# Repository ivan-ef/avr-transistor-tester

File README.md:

# AVR Transistor Tester

Component/Transistor tester based on famous [AVR Transistor Tester](https://www.mikrocontroller.net/articles/AVR_Transistortester) project. The reason I decided to create a custom PCB is that currently there is not good kit or complete device available that would fit my wishes:

- ATMega644 MCU
- 2.4" 65K colors LCD
- Rotary encoder
- USB-C charger with Li-Po battery
- Higher grade/precision components

Most of Chinese versions are starting to use fake or non-original Microchip MCUs that prevents their software upgrades and economy on components makes them less accurate. I didn't include a lot of hardware options, because I primarily using the device for measuring passive components and transistors used in guitar pedals building.

## Complete unit

## PCB

I used SMD assembly service at JLCPCB and ended up with a set 5 PCBs cost around 25$ each. But since SMD components used there is not the smallest size ones, it is 100% possible to solder everything by hand.

## Schematic

[PDF](https://github.com/vitaliy-bobrov/avr-transistor-tester/blob/main/schematic.pdf)

## Hardware

PCB has almost everything as SMD assembly and requires a few components to be soldered by hand:

- Rotary Encoder - basically any common one would work here, but I've used BOURNS PEC11R-4220K-S0024. It is available at most big components suppliers. My personal choice was [TME](https://www.tme.eu/pl/details/pec11r-4220k-s0024/enkodery-inkrementalne/bourns/).
- ZIF 14 pin socket - again you could use any common one. I used CONNFLY DS1044-140G from [TME](https://www.tme.eu/pl/details/ds1044-140g/podstawki-testowe/connfly/)
- 2.4" 65K colors LCB. Not sure if other ILI9341 controller based would have the same pins/size. I used [Waveshare 18366](https://www.waveshare.com/2.4inch-lcd-module.htm) which is not expensive and commonly available. At [TME](https://www.tme.eu/pl/details/wsh-18366/wyswietlacze-lcd-graficzne/waveshare/18366/) too ;)
- 2.54mm spaced 2x3 pins for ISP - this could be left without pins soldered, then just ensure you have good contact between the PCB and programming pins.
- 2.54mm 3 pin socket for components/transistors - just alternative for ZIF socket
- Any Li-Po or Li-Ion battery with work with the charger IC, but the PCB was designed with Li-Po in mind due to size. I used [550mA battery](https://www.tme.eu/pl/details/aky-lp503040/akumulatory/akyga-battery/aky0185/), but you could use any other that would fit about 55x50mm size.

## Software

The software used in m-software version 1.55m (see [docs](https://github.com/madires/Transistortester-Warehouse/tree/master/Documentation)), but k-software could be used as well. The pins assignment is based on project docs suggested one. Precompiled version is in the [software](https://github.com/vitaliy-bobrov/avr-transistor-tester/blob/main/software/) folder.

### Software compilation

1. Install AVR tools for your operating system and programmer you are using (ex. avrdude)
2. Navigate to software folder
3. Run `make`
4. Connect programmer to the ISP pins on the PCB
5. Run `make fuses` to set MCU fuses
6. Run `make upload` to upload firmware

## Enclosure

I designed a simple 3D printable enclosure that fits the PCB and provides easy access to ISP pins and USB-C charger. STEP files are located in the [3d-enclosure](https://github.com/vitaliy-bobrov/avr-transistor-tester/blob/main/3d-enclosure/) folder. Printing profile is available at [MakerWorld](https://makerworld.com/en/models/883799#profileId-838469) which would be handy if you have a BambuLab 3D printer.

The assembled PCB with display is mounted to enclosure using spacers that came with Waveshare display using 4 x M2x8mm and 4 x M2x16mm screws. the battery is fixed on the backplate with double sided 3M foam.

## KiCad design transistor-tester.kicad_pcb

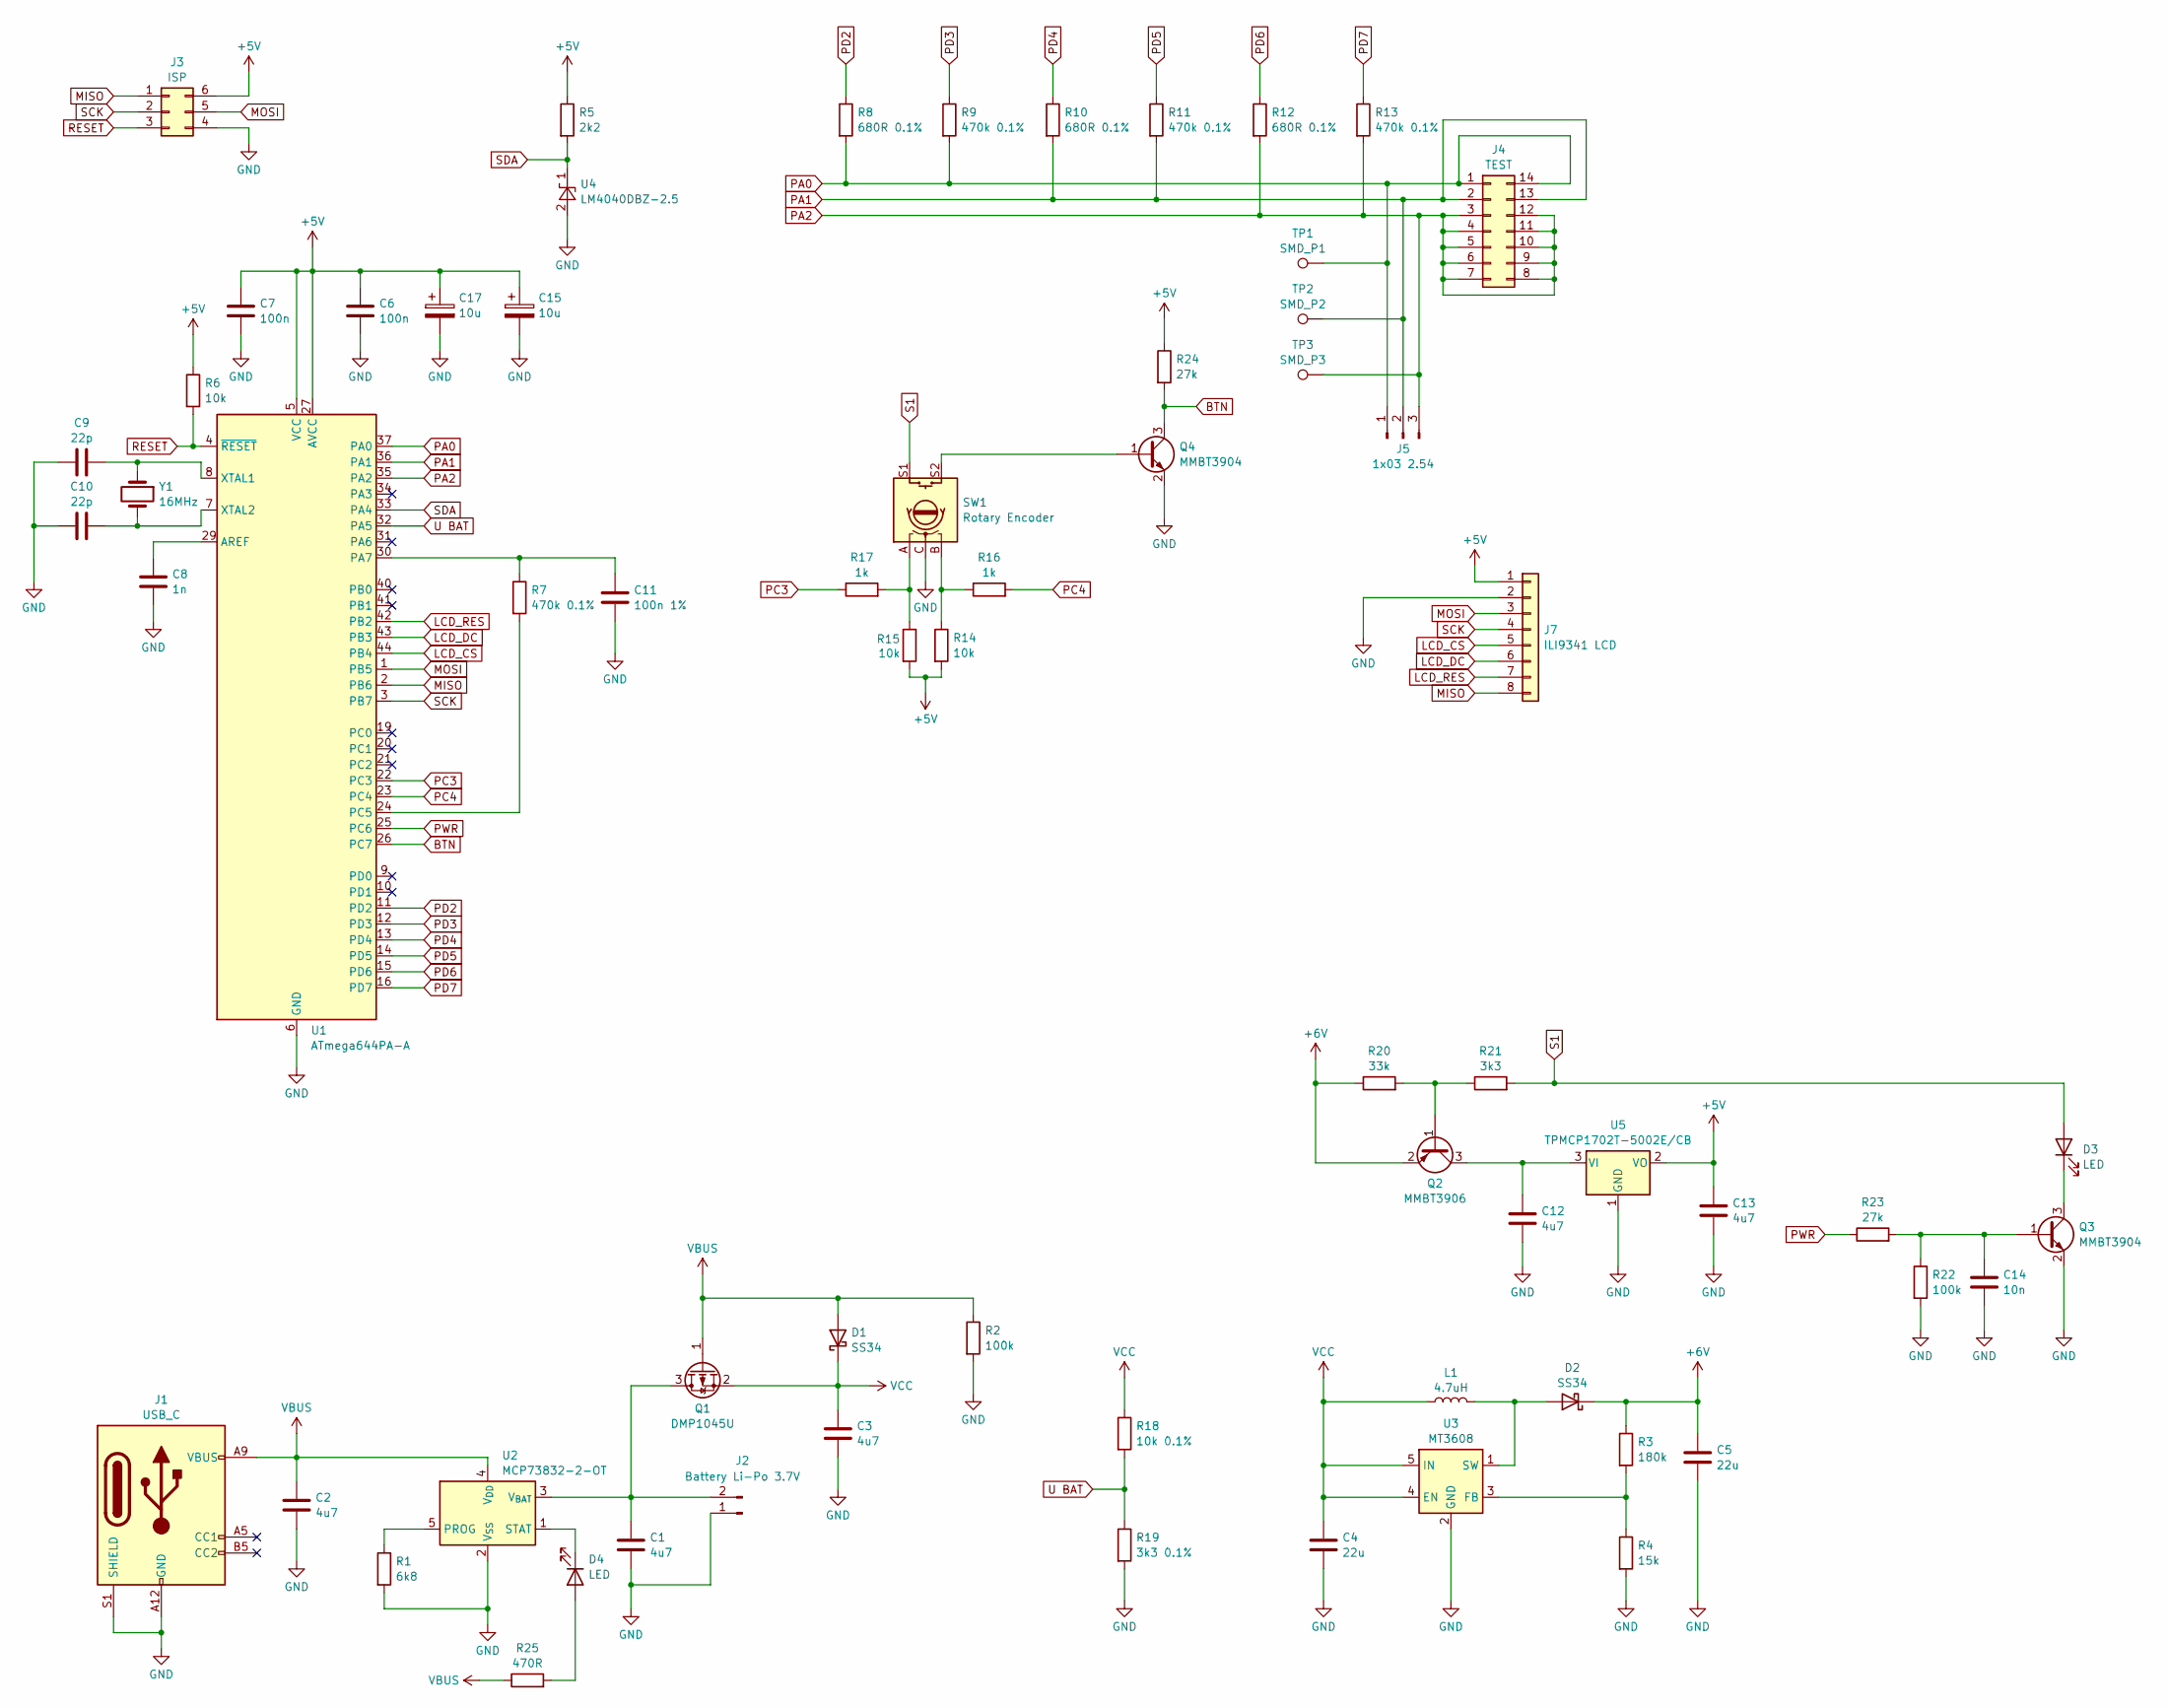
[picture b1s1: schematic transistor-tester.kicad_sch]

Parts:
C1, C2, C3, C12, C13: 4u7; C_1206_3216Metric; JLCPCB Part # C29823
C4, C5: 22u; C_0805_2012Metric; JLCPCB Part # C45783
C6, C7: 100n; C_0805_2012Metric
C8: 1n; C_0805_2012Metric
C9, C10: 22p; C_0805_2012Metric; JLCPCB Part # C1804
C11: 100n 1%; C_0805_2012Metric; JLCPCB Part # C2981728
C14: 10n; C_0805_2012Metric; JLCPCB Part # C1710
C15, C17: 10u; CP_EIA-3216-18_Kemet-A; JLCPCB Part # C7171
D1, D2: SS34; D_SMA; JLCPCB Part # C8678
D3, D4: LED; LED_0805_2012Metric; JLCPCB Part # C84256
J1: USB_C; USB_C_Receptacle_GCT_USB4125-xx-x-0190_6P_TopMnt_Horizontal; JLCPCB Part # C283540
J2: Battery Li-Po 3.7V; PinHeader_1x02_P2.54mm_Vertical
J3: ISP; PinHeader_2x03_P2.54mm_Vertical
J4: TEST; DIP_Socket-14_W4.3_W5.08_W7.62_W10.16_W10.9_3M_214-3339-00-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
J5: 1x03 2.54; TO-92L_Inline_Wide
J7: ILI9341 LCD; Waveshare_2.4_ILI9341_18366
L1: 4.7uH; L_1206_3216Metric; JLCPCB Part # C2941590
Q1: DMP1045U; SOT-23; JLCPCB Part # C177033
Q2: MMBT3906; SOT-23
Q3, Q4: MMBT3904; SOT-23
R1: 6k8; R_0805_2012Metric
R2, R22: 100k; R_0805_2012Metric
R3: 180k; R_0805_2012Metric
R4: 15k; R_0805_2012Metric
R5: 2k2; R_0805_2012Metric
R6, R14, R15: 10k; R_0805_2012Metric
R7, R9, R11, R13: 470k 0.1%; R_0805_2012Metric
R8, R10, R12: 680R 0.1%; R_0805_2012Metric
R16, R17: 1k; R_0805_2012Metric
R18: 10k 0.1%; R_0805_2012Metric
R19: 3k3 0.1%; R_0805_2012Metric
R20: 33k; R_0805_2012Metric
R21: 3k3; R_0805_2012Metric
R23, R24: 27k; R_0805_2012Metric
R25: 470R; R_0805_2012Metric
SW1: Rotary Encoder; RotaryEncoder_Alps_EC12E-Switch_Vertical_H20mm
TP1: SMD_P1; TestPoint_Pad_1.5x1.5mm
TP2: SMD_P2; TestPoint_Pad_1.5x1.5mm
TP3: SMD_P3; TestPoint_Pad_3.0x3.0mm
U1: ATmega644PA-A; TQFP-44_10x10mm_P0.8mm; JLCPCB Part # C38349
U2: MCP73832-2-OT; SOT-23-5; JLCPCB Part # C38066
U3: MT3608; SOT-23-6; JLCPCB Part # C2932326
U4: LM4040DBZ-2.5; SOT-23; JLCPCB Part # C9421
U5: TPMCP1702T-5002E/CB; SOT-23; JLCPCB Part # C3040636
Y1: 16MHz; Crystal_SMD_HC49-SD; JLCPCB Part # C12676

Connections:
+5V: C6.1, C7.1, C13.1, C15.1, C17.1, J3.6, J7.1, R5.1, R6.1, R14.2, R15.2, R24.1, U1.5 (VCC), U1.17 (VCC), U1.27 (AVCC), U1.38 (VCC), U5.2 (VO)
+6V: C5.1, D2.1 (K), Q2.2 (E), R3.1, R20.1
BTN: Q4.3 (C), R24.2, U1.26 (PC7)
GND: C1.2, C2.2, C3.2, C4.2, C5.2, C6.2, C7.2, C8.2, C9.2, C10.2, C11.2, C12.2, C13.2, C14.2, C15.2, C17.2, J1.A12 (GND), J1.B12 (GND), J1.S1 (SHIELD), J2.1, J3.4, J7.2, Q3.2 (E), Q4.2 (E), R1.2, R2.2, R4.2, R19.2, R22.2, SW1.C, U1.6 (GND), U1.18 (GND), U1.28 (GND), U1.39 (GND), U2.2 (V_{SS}), U3.2 (GND), U4.2 (A), U5.1 (GND)
LCD_CS: J7.5, U1.44 (PB4)
LCD_DC: J7.6, U1.43 (PB3)
LCD_RES: J7.7, U1.42 (PB2)
MISO: J3.1, J7.8, U1.2 (PB6)
MOSI: J3.5, J7.3, U1.1 (PB5)
unnamed: D2.2 (A), L1.2, U3.1 (SW)
unnamed: D3.1 (K), Q3.3 (C)
unnamed: D4.2 (A), R25.2
unnamed: D4.1 (K), U2.1 (STAT)
unnamed: C1.1, J2.2, Q1.3 (D), U2.3 (V_{BAT})
unnamed: Q2.1 (B), R20.2, R21.1
unnamed: C12.1, Q2.3 (C), U5.3 (VI)
unnamed: C14.1, Q3.1 (B), R22.1, R23.2
unnamed: Q4.1 (B), SW1.S2
unnamed: R14.1, R16.1, SW1.B
unnamed: R15.1, R17.2, SW1.A
unnamed: C8.1, U1.29 (AREF)
unnamed: C11.1, R7.1, U1.30 (PA7)
unnamed: R7.2, U1.24 (PC5)
unnamed: C9.1, U1.8 (XTAL1), Y1.1
unnamed: C10.1, U1.7 (XTAL2), Y1.2
unnamed: R1.1, U2.5 (PROG)
unnamed: R3.2, R4.1, U3.3 (FB)
PA0: J4.1, J4.14, J5.1, R8.2, R9.2, TP1.1, U1.37 (PA0)
PA1: J4.2, J4.13, J5.2, R10.2, R11.2, TP2.1, U1.36 (PA1)
PA2: J4.3, J4.4, J4.5, J4.6, J4.7, J4.8, J4.9, J4.10, J4.11, J4.12, J5.3, R12.2, R13.2, TP3.1, U1.35 (PA2)
PC3: R17.1, U1.22 (PC3)
PC4: R16.2, U1.23 (PC4)
PD2: R8.1, U1.11 (PD2)
PD3: R9.1, U1.12 (PD3)
PD4: R10.1, U1.13 (PD4)
PD5: R11.1, U1.14 (PD5)
PD6: R12.1, U1.15 (PD6)
PD7: R13.1, U1.16 (PD7)
PWR: R23.1, U1.25 (PC6)
RESET: J3.3, R6.2, U1.4 (~RESET)
S1: D3.2 (A), R21.2, SW1.S1
SCK: J3.2, J7.4, U1.3 (PB7)
SDA: R5.2, U1.33 (PA4), U4.1 (K)
U BAT: R18.2, R19.1, U1.32 (PA5)
VBUS: C2.1, D1.2 (A), J1.A9 (VBUS), J1.B9 (VBUS), Q1.1 (G), R2.1, R25.1, U2.4 (V_{DD})
VCC: C3.1, C4.1, D1.1 (K), L1.1, Q1.2 (S), R18.1, U3.4 (EN), U3.5 (IN)

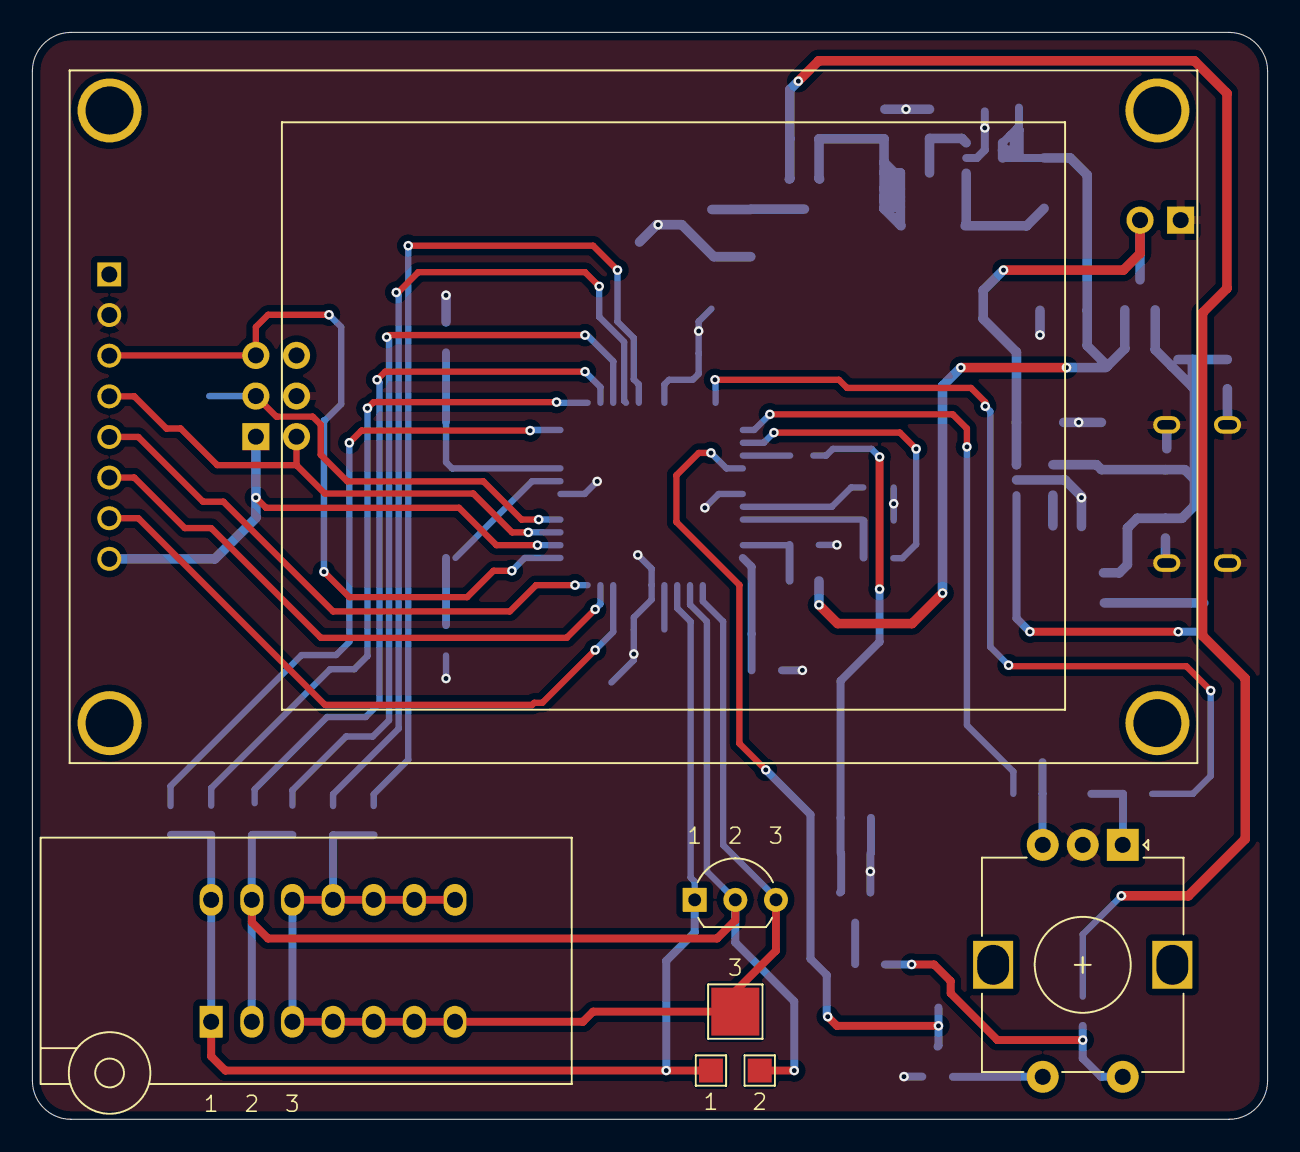
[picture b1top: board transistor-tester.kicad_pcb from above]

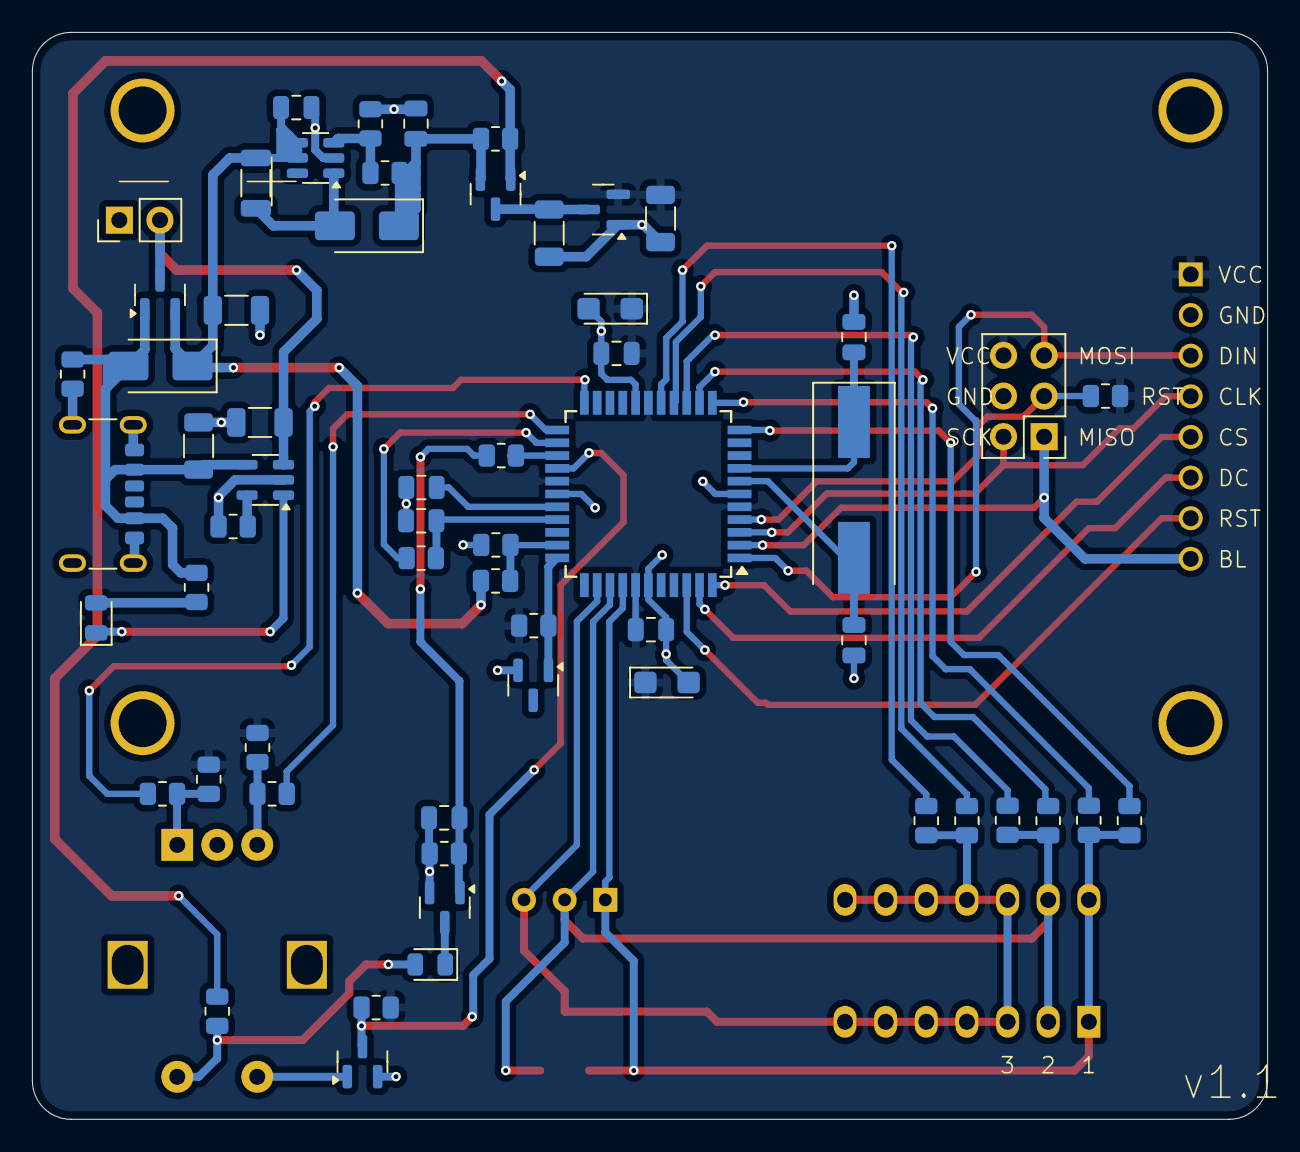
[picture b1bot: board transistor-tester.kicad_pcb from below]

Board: 2 copper layers, 77.2 x 67.9 mm, 66 parts (59 on the bottom side), 46 nets.

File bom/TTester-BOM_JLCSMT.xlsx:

Comment | Designator | Footprint | LCSC Part #（optional）
16MHz | Y1 | Crystal_SMD_HC49-SD | C12676
TPMCP1702T-5002E/CB | U5 | SOT-23 | C3040636
LM4040DBZ-2.5 | U4 | SOT-23 | C9421
MT3608 | U3 | SOT-23-6 | C2932326
MCP73832-2-OT | U2 | SOT-23-5 | C38066
ATmega644PA-A | U1 | TQFP-44_10x10mm_P0.8mm | C38349
470R | R25 | R_0805_2012Metric
27k | R24,R23 | R_0805_2012Metric
100k | R22,R2 | R_0805_2012Metric
3k3 | R21 | R_0805_2012Metric
33k | R20 | R_0805_2012Metric
3k3 0.1% | R19 | R_0805_2012Metric | C2989690
10k 0.1% | R18 | R_0805_2012Metric | C5159707
1k | R17,R16 | R_0805_2012Metric
10k | R15,R14,R6,R1 | R_0805_2012Metric
470k 0.1% | R13,R11,R9,R7 | R_0805_2012Metric | C316216
680R 0.1% | R12,R10,R8 | R_0805_2012Metric | C2988999
2k2 | R5 | R_0805_2012Metric
15k | R4 | R_0805_2012Metric
120k | R3 | R_0805_2012Metric
MMBT3904 | Q4,Q3 | SOT-23 | C20526
MMBT3906 | Q2 | SOT-23 | C53444
DMP1045U | Q1 | SOT-23 | C177033
4.7uH | L1 | L_1206_3216Metric | C2941590
USB_C | J1 | USB_C_Receptacle_GCT_USB4125-xx-x-0190_6P_TopMnt_Horizontal | C283540
LED | D4,D3 | LED_0805_2012Metric | C84256
SS34 | D2,D1 | D_SMA
10u | C17,C15 | CP_EIA-3216-18_Kemet-A | C7171
10n | C14 | C_0805_2012Metric
4u7 | C13,C12,C3,C2,C1 | C_1206_3216Metric | C29823
100n 10% | C11 | C_0805_2012Metric | C476766
22p | C10,C9 | C_0805_2012Metric | C1804
1n | C8 | C_0805_2012Metric
100n | C7,C6 | C_0805_2012Metric
22u | C5,C4 | C_0805_2012Metric | C45783

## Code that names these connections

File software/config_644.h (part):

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#define LCD_PORT         PORTB          /* port data register */
#define LCD_DDR          DDRB           /* port data direction register */
//#define LCD_DB_STD                      /* use standard pins 0-3 for DB4-7 */
#define LCD_DB4          PB4            /* port pin used for DB4 */
#define LCD_DB5          PB5            /* port pin used for DB5 */
#define LCD_DB6          PB6            /* port pin used for DB6 */
#define LCD_DB7          PB7            /* port pin used for DB7 */
#define LCD_RS           PB2            /* port pin used for RS */
#define LCD_EN1          PB3            /* port pin used for E */
/* display settings */
#define LCD_CHAR_X       16             /* characters per line */
#define LCD_CHAR_Y       2              /* number of lines */
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/* control and data lines */
#define LCD_PORT         PORTB          /* port data register */
#define LCD_DDR          DDRB           /* port data direction register */
#define LCD_RES          PB2            /* port pin used for /RESX (optional) */
#define LCD_CS           PB4            /* port pin used for /CSX (optional) */
#define LCD_DC           PB3            /* port pin used for D/CX */
#define LCD_SCL          PB7            /* port pin used for SCL */
#define LCD_SDA          PB5            /* port pin used for SDA/SDIO */
/* display settings */
#define LCD_DOTS_X       128            /* number of horizontal dots */
#define LCD_DOTS_Y       128            /* number of vertical dots */
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/* control and data lines */
#define LCD_PORT         PORTB          /* port data register */
#define LCD_DDR          DDRB           /* port data direction register */
#define LCD_RES          PB2            /* port pin used for /RES (optional) */
#define LCD_CS           PB4            /* port pin used for /CS (optional) */
#define LCD_DC           PB3            /* port pin used for D/C */
#define LCD_SCK          PB7            /* port pin used for SCK */
#define LCD_SDI          PB5            /* port pin used for SDI (data input) */
#define LCD_SDO          PB6            /* port pin used for SDO (data output) */
/* display settings */
#define LCD_DOTS_X       320            /* number of horizontal dots */
#define LCD_DOTS_Y       240            /* number of vertical dots */
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/* control lines */
#define LCD_PORT         PORTC          /* port data register */
#define LCD_DDR          DDRC           /* port data direction register */
#define LCD_RES          PC4            /* port pin used for /RESX (optional) */
#define LCD_CS           PC3            /* port pin used for /CSX (optional) */
#define LCD_DC           PC2            /* port pin used for D/CX */
#define LCD_WR           PC1            /* port pin used for WRX */
#define LCD_RD           PC0            /* port pin used for RDX (optional) */
/* data lines DB0-7 */
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#define LCD_PIN2         PINB           /* port data direction register */
#define LCD_DB0          PB0            /* port pin used for DB0 */
#define LCD_DB1          PB1            /* port pin used for DB1 */
#define LCD_DB2          PB2            /* port pin used for DB2 */
#define LCD_DB3          PB3            /* port pin used for DB3 */
#define LCD_DB4          PB4            /* port pin used for DB4 */
#define LCD_DB5          PB5            /* port pin used for DB5 */
#define LCD_DB6          PB6            /* port pin used for DB6 */
#define LCD_DB7          PB7            /* port pin used for DB7 */
/* display settings */
#define LCD_DOTS_X       320            /* number of horizontal dots */
#define LCD_DOTS_Y       480            /* number of vertical dots */
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/* control and data lines */
#define LCD_PORT         PORTB          /* port data register */
#define LCD_DDR          DDRB           /* port data direction register */
#define LCD_RES          PB2            /* port pin used for /RES (optional) */
#define LCD_CS           PB4            /* port pin used for /CS (optional) */
#define LCD_DC           PB3            /* port pin used for D/C */
#define LCD_SCL          PB7            /* port pin used for SCL */
#define LCD_SDA          PB5            /* port pin used for DIN/SDA (data input) */
//#define LCD_SDO          PB6            /* port pin used for DOUT/SDO (data output) */
/* display settings */
#define LCD_DOTS_X       320            /* number of horizontal dots */
#define LCD_DOTS_Y       480            /* number of vertical dots */
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/* control and data lines */
#define LCD_PORT         PORTB          /* port data register */
#define LCD_DDR          DDRB           /* port data direction register */
#define LCD_RES          PB2            /* port pin used for /RES (optional) */
#define LCD_SCE          PB4            /* port pin used for /SCE (optional) */
#define LCD_DC           PB3            /* port pin used for D/C */
#define LCD_SCLK         PB7            /* port pin used for SCLK */
#define LCD_SDIN         PB5            /* port pin used for SDIN (data input) */
/* display settings */
#define LCD_DOTS_X       84             /* number of horizontal dots */
#define LCD_DOTS_Y       48             /* number of vertical dots */
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/* control and data lines */
#define LCD_PORT         PORTB          /* port data register */
#define LCD_DDR          DDRB           /* port data direction register */
#define LCD_RESET        PB2            /* port pin used for /RES */
#define LCD_CS           PB4            /* port pin used for /CS (optional) */
#define LCD_SCLK         PB7            /* port pin used for SCLK */
#define LCD_SDIN         PB5            /* port pin used for SDIN (data input) */
/* display settings */
#define LCD_DOTS_X       96             /* number of horizontal dots */
#define LCD_DOTS_Y       65             /* number of vertical dots */
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/* control and data lines */
#define LCD_PORT         PORTB          /* port data register */
#define LCD_DDR          DDRB           /* port data direction register */
#define LCD_RESET        PB2            /* port pin used for /RES (optional) */
#define LCD_CS           PB4            /* port pin used for /CS (optional) */
#define LCD_A0           PB3            /* port pin used for A0 */
#define LCD_SCL          PB7            /* port pin used for SCL */
#define LCD_SI           PB5            /* port pin used for SI (data input) */
/* display settings */
#define LCD_DOTS_X       128            /* number of horizontal dots */
#define LCD_DOTS_Y       64             /* number of vertical dots */
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/* control and data lines */
#define LCD_PORT         PORTB          /* port data register */
#define LCD_DDR          DDRB           /* port data direction register */
#define LCD_RESET        PB2            /* port pin used for /RES (optional) */
#define LCD_CS           PB4            /* port pin used for /CS (optional) */
#define LCD_SCL          PB7            /* port pin used for SCL */
#define LCD_SI           PB5            /* port pin used for SI (data input) */
/* display settings */
#define LCD_DOTS_X       128            /* number of horizontal dots */
#define LCD_DOTS_Y       64             /* number of vertical dots */
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/* control lines */
#define LCD_PORT         PORTB          /* port data register */
#define LCD_DDR          DDRB           /* port data direction register */
//#define LCD_RESET        PB2            /* port pin used for /RES (optional) */
/* display settings */
#define LCD_DOTS_X       128            /* number of horizontal dots */
#define LCD_DOTS_Y       64             /* number of vertical dots */
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/* control and data lines */
#define LCD_PORT         PORTB          /* port data register */
#define LCD_DDR          DDRB           /* port data direction register */
#define LCD_RESET        PB2            /* port pin used for /RES (optional) */
#define LCD_CS           PB4            /* port pin used for /CS (optional) */
#define LCD_DC           PB3            /* port pin used for D/C */
#define LCD_SCLK         PB7            /* port pin used for SCLK */
#define LCD_SDIN         PB5            /* port pin used for SDIN (data input) */
/* display settings */
#define LCD_DOTS_X       128            /* number of horizontal dots */
#define LCD_DOTS_Y       64             /* number of vertical dots */
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/* control and data lines */
#define LCD_PORT         PORTB          /* port data register */
#define LCD_DDR          DDRB           /* port data direction register */
#define LCD_RESET        PB2            /* port pin used for /RES (optional) */
#define LCD_CS           PB4            /* port pin used for /CS (optional) */
#define LCD_SCLK         PB7            /* port pin used for SCLK */
#define LCD_SDIN         PB5            /* port pin used for SDIN (data input) */
/* display settings */
#define LCD_DOTS_X       128            /* number of horizontal dots */
#define LCD_DOTS_Y       64             /* number of vertical dots */
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/* control lines */
#define LCD_PORT         PORTB          /* port data register */
#define LCD_DDR          DDRB           /* port data direction register */
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
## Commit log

2024-12-15 intial commit
2024-12-15 Added MakerWorld link
2024-12-24 Minor fixes
2025-04-22 Update BOM
2025-04-22 software 1.55m update
2025-04-22 Software update 1.55m
2025-04-22 fix Ge BJT detection
2025-10-30 Add files via upload
    add LCSC Part #
2025-10-30 add missing LCSC Part #
2025-10-30 cpl Pick&Place file for JLCPCB
    pick and place file generated from gerber in kicad. partially reformatted according to JLCPCB support manual with chatGPT, tested on JLCPCB site assembly section.

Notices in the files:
software/config_644.h:
(c) 2012-2024 by Markus Reschke
